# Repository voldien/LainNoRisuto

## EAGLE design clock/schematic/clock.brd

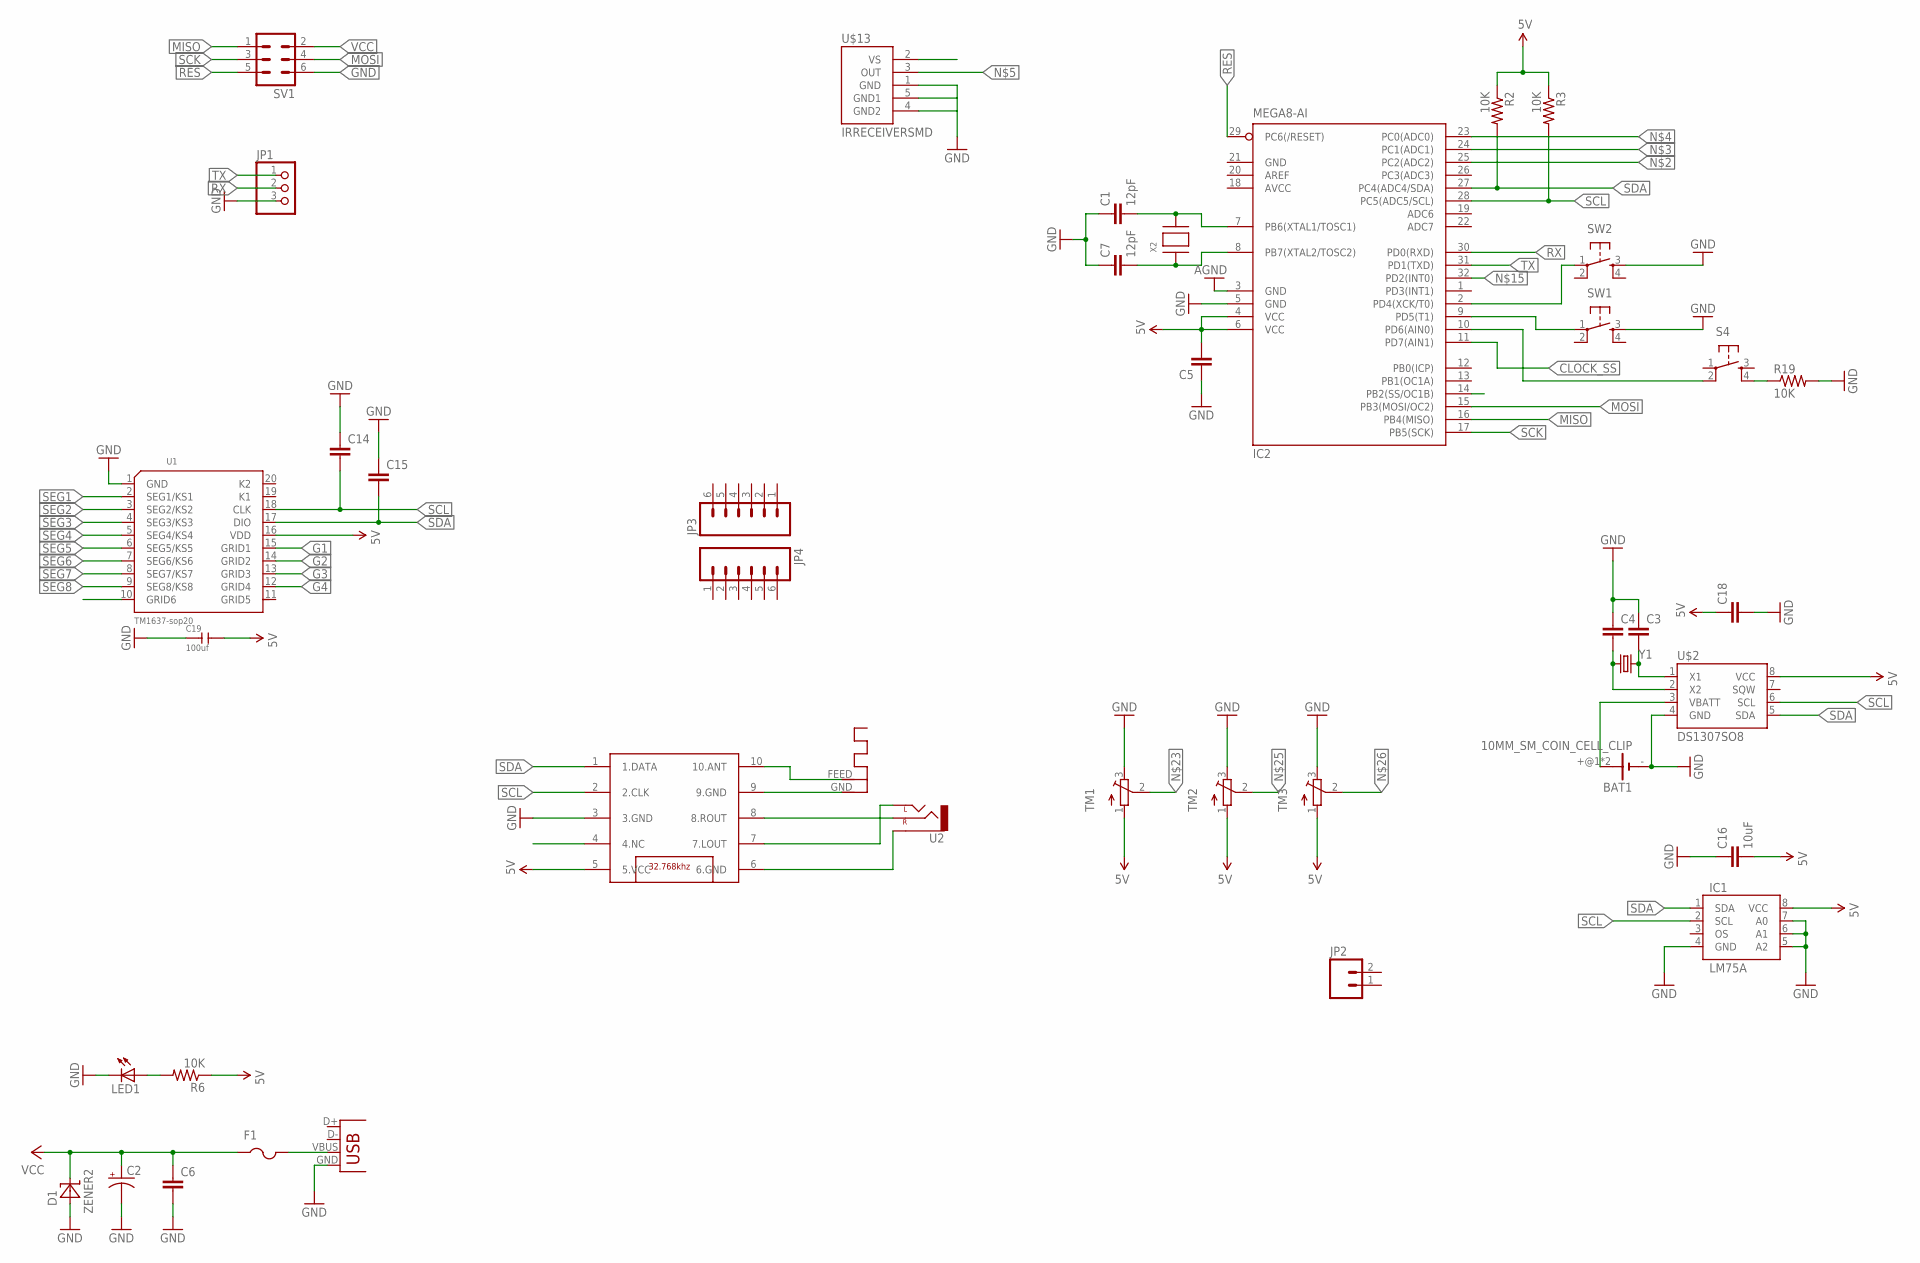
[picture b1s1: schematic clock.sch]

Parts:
ANT1: ANTENNA; RN-ANT
BAT1: 10MM_SM_COIN_CELL_CLIP
C1, C7: 12pF; C0603
C2: CPOL-USB; PANASONIC_B
C3, C4, C5, C6, C14, C15, C18: C-EUC0603; C0603
C16: 10uF; C0603
C19: 100uf; C1206
D1: ZENER2; SOD123
F1: PTCFUSE-1206; R1206
IC1: LM75A; SO8
IC2: MEGA8-AI; TQFP32-08
JP1: PINHD-1X3CB; 1X03-CLEANBIG
JP2: M02PTH; 1X02
JP3, JP4: M06SIP; 1X06
LED1: LED0603; LED-0603
R2, R3, R6, R19: 10K; R0603
S4: TAC_SWITCHSMD; TACTILE_SWITCH_SMD
SV1: MA03-2
SW1, SW2: TAC_SWITCHSMD; TACTILE_SWITCH_SMD
TM1, TM2, TM3: TRIMPOTTC33X; TC33X
U1: TM1637-sop20; SOP20-1.27-12.7X7.65MM
U2: AUDIO-JACKSMD; STEREOJACK2.5MM_SMD
U$2: DS1307SO8; SO08
U$13: IRRECEIVERSMD; TSOP8523
U$14: TEA5767; TJ-102BC
X1: USB-MICROB
X2: XTAL-3.2X1.5; XTAL3215
Y1: CRYSTALTC26H; TC26H

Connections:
5V: C5.2, C16.2, C18.1, C19.2, IC1.8 (VCC), IC2.4 (VCC), IC2.6 (VCC), R2.1, R3.1, R6.1, TM1.1 (A), TM2.1 (A), TM3.1 (A), U1.16 (VDD), U$2.8 (VCC), U$14.5 (5.VCC)
AGND: IC2.3 (GND)
AVCC: IC2.18 (AVCC)
CLOCK_SS: IC2.11 (PD7(AIN1))
G1: U1.15 (GRID1)
G2: U1.14 (GRID2)
G3: U1.13 (GRID3)
G4: U1.12 (GRID4)
GND: BAT1.-, C1.1, C2.-, C3.1, C4.1, C5.1, C6.2, C7.1, C14.1, C15.1, C16.1, C18.2, C19.1, D1.A, IC1.4 (GND), IC1.5 (A2), IC1.6 (A1), IC1.7 (A0), IC2.5 (GND), IC2.21 (GND), JP1.3, LED1.C, R19.2, SV1.6, SW1.3, SW2.3, TM1.3 (E), TM2.3 (E), TM3.3 (E), U1.1 (GND), U$2.4 (GND), U$13.1 (GND), U$13.4 (GND2), U$13.5 (GND1), U$14.3 (3.GND), X1.GND
MISO: IC2.16 (PB4(MISO)), SV1.1
MOSI: IC2.15 (PB3(MOSI/OC2)), SV1.4
unnamed: U2.5 (SLEEVE), U$14.6 (6.GND)
unnamed: U2.4 (RIGHT), U$14.8 (8.ROUT)
unnamed: BAT1.+@1 (+), BAT1.+@2 (+), U$2.3 (VBATT)
unnamed: U2.1 (LEFT), U$14.7 (7.LOUT)
unnamed: C4.2, U$2.2 (X2), Y1.1
unnamed: C3.2, U$2.1 (X1), Y1.2
unnamed: ANT1.FEED, U$14.10 (10.ANT)
unnamed: IC2.9 (PD5(T1)), SW1.1
unnamed: ANT1.GND, U$14.9 (9.GND)
unnamed: IC2.2 (PD4(XCK/T0)), SW2.1
unnamed: IC2.10 (PD6(AIN0)), S4.2
unnamed: F1.2, X1.VBUS
unnamed: C1.2, IC2.7 (PB6(XTAL1/TOSC1)), X2.P$2
unnamed: R19.1, S4.4
unnamed: C7.2, IC2.8 (PB7(XTAL2/TOSC2)), X2.P$1
unnamed: LED1.A, R6.2
RES: IC2.29 (PC6(/RESET)), SV1.5
RX: IC2.30 (PD0(RXD)), JP1.2
SCK: IC2.17 (PB5(SCK)), SV1.3
SCL: C14.2, IC1.2 (SCL), IC2.28 (PC5(ADC5/SCL)), R3.2, U1.18 (CLK), U$2.6 (SCL), U$14.2 (2.CLK)
SDA: C15.2, IC1.1 (SDA), IC2.27 (PC4(ADC4/SDA)), R2.2, U1.17 (DIO), U$2.5 (SDA), U$14.1 (1.DATA)
SEG1: U1.2 (SEG1/KS1)
SEG2: U1.3 (SEG2/KS2)
SEG3: U1.4 (SEG3/KS3)
SEG4: U1.5 (SEG4/KS4)
SEG5: U1.6 (SEG5/KS5)
SEG6: U1.7 (SEG6/KS6)
SEG7: U1.8 (SEG7/KS7)
SEG8: U1.9 (SEG8/KS8)
TX: IC2.31 (PD1(TXD)), JP1.1
VCC: C2.+, C6.1, D1.C, F1.1, SV1.2

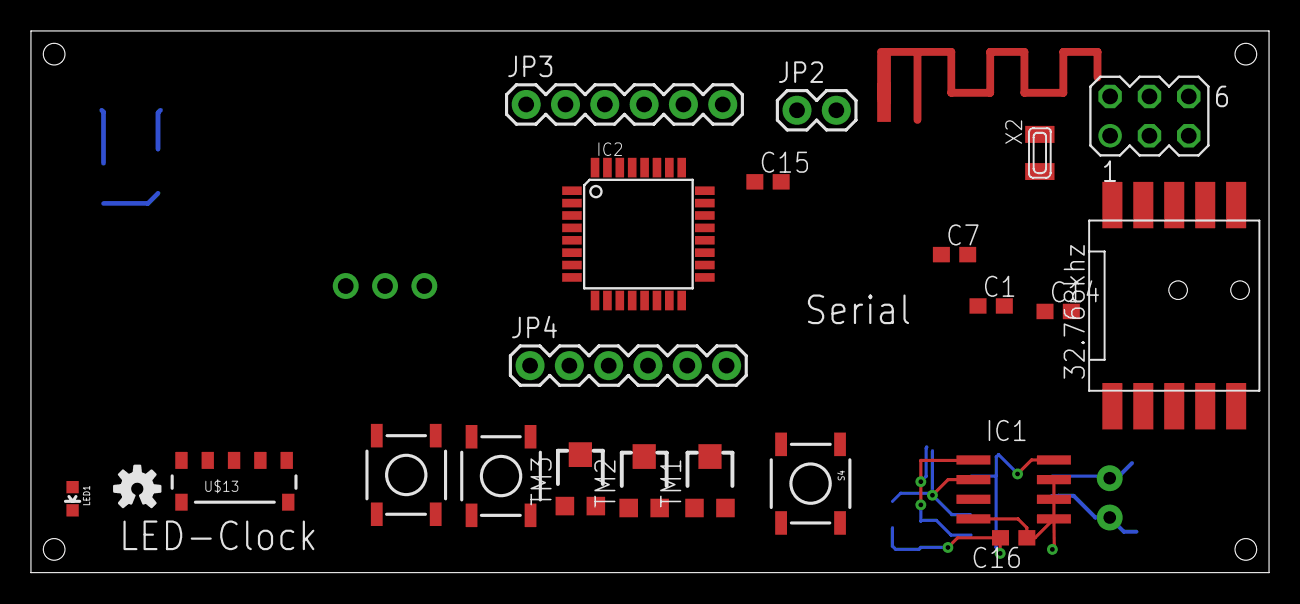
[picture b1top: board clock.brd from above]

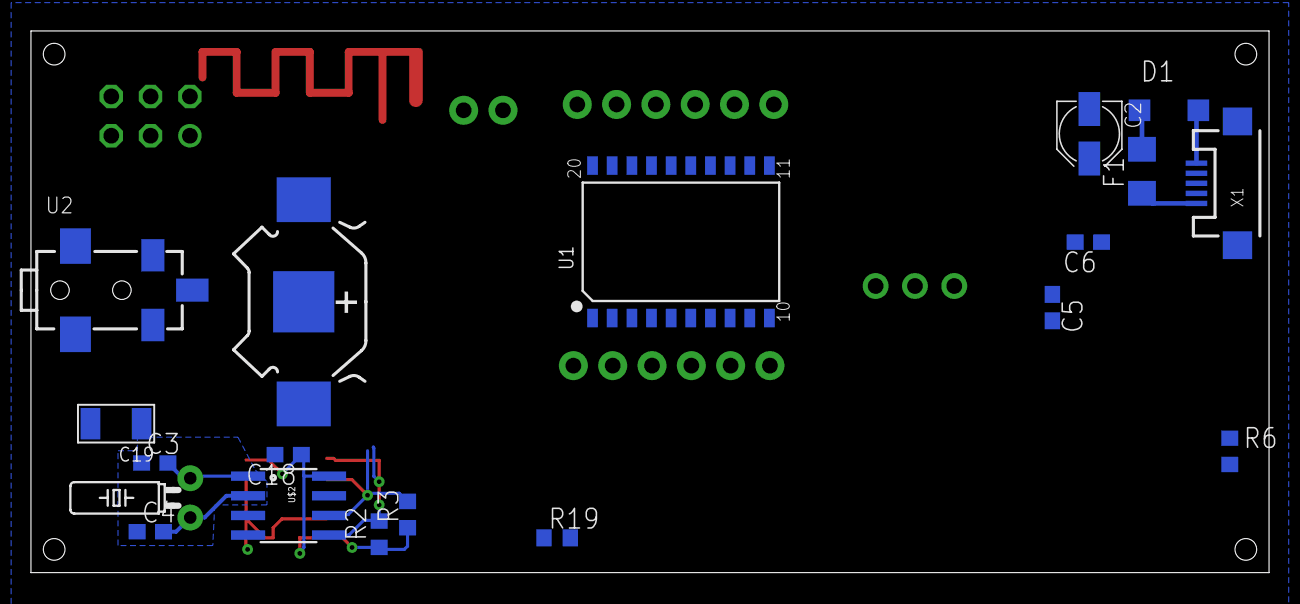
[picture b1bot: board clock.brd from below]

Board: 2 copper layers, 80.0 x 35.0 mm, 43 parts (19 on the bottom side), 27 nets.

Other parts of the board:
U$6: OSHW-LOGO-S

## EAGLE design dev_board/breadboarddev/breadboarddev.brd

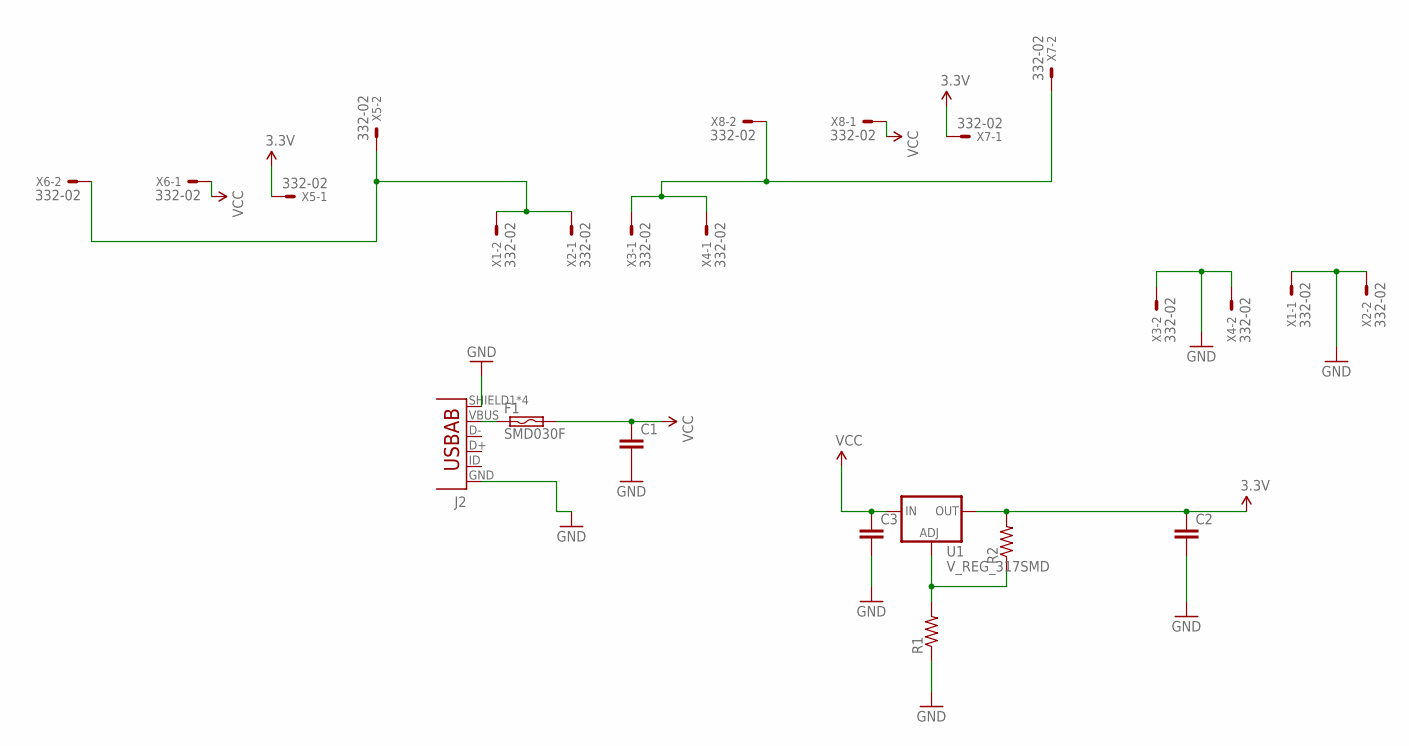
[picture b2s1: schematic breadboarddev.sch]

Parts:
C1, C2, C3: C-EUC0603K; C0603K
F1: SMD030F; SMD050F
J2: USB-AB; USB-AB-MICRO-SMD
R1, R2: R-US_MELF0204W; MINI_MELF-0204W
U1: V_REG_317SMD; SOT223
X1, X2, X3, X4, X5, X6, X7, X8: 332-02

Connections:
3.3V: C2.1, R2.2, U1.2 (OUT), X5.1, X7.1
GND: C1.2, C2.2, C3.2, J2.GND, J2.SHIELD1 (SHIELD), J2.SHIELD2 (SHIELD), J2.SHIELD3 (SHIELD), J2.SHIELD4 (SHIELD), R1.1, X1.1, X2.2, X3.2, X4.2
unnamed: R1.2, R2.1, U1.1 (ADJ)
unnamed: X1.2, X2.1, X5.2, X6.2
unnamed: F1.1, J2.VBUS
unnamed: X3.1, X4.1, X7.2, X8.2
VCC: C1.1, C3.1, F1.2, U1.3 (IN), X6.1, X8.1

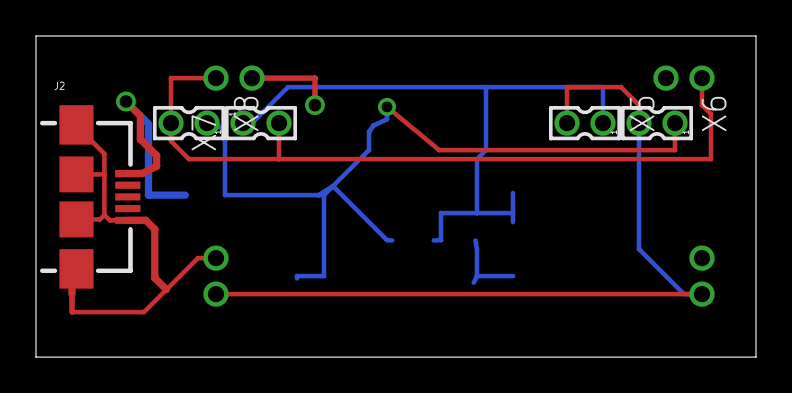
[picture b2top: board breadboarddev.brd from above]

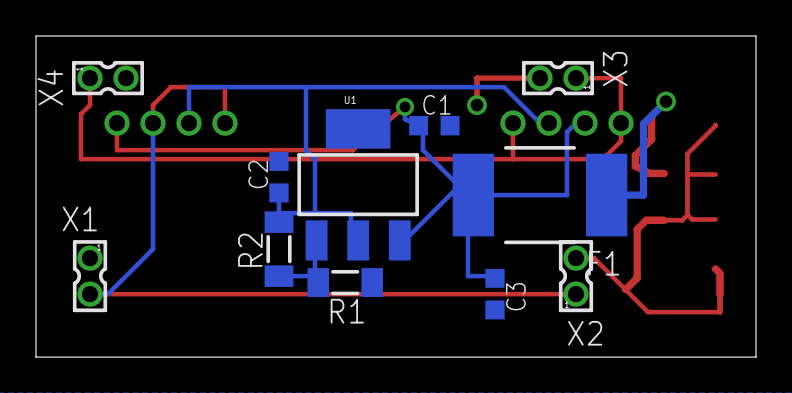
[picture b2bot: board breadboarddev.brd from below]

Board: 2 copper layers, 40.0 x 17.8 mm, 17 parts (11 on the bottom side), 7 nets.

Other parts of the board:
U$1: OSHWLOGO_TOL_0.2

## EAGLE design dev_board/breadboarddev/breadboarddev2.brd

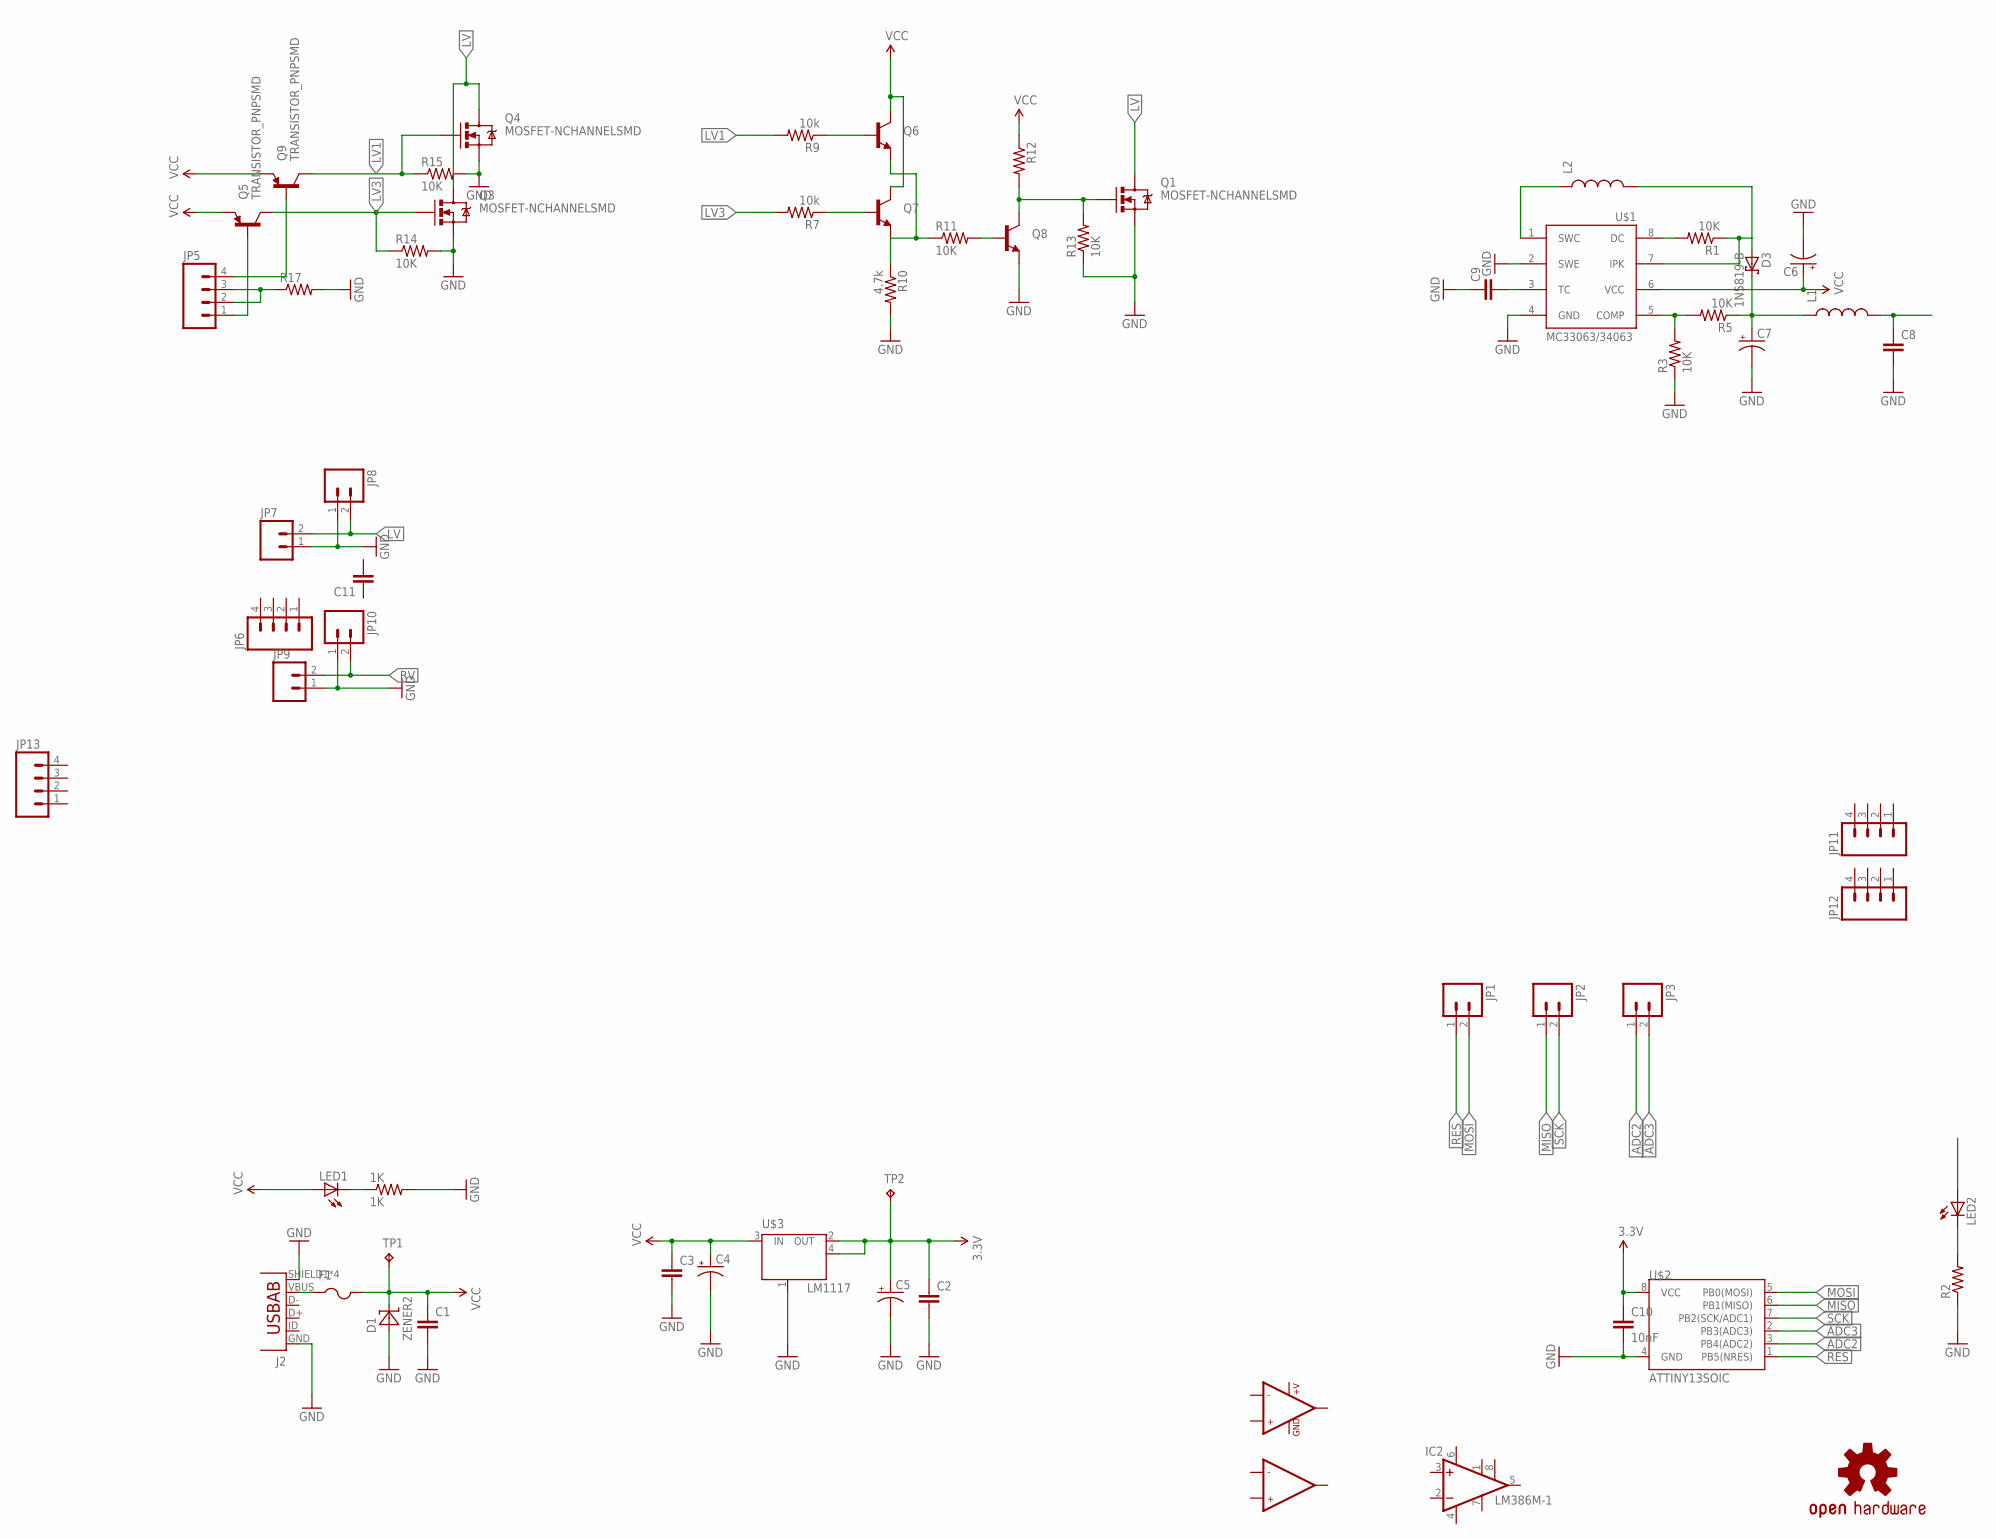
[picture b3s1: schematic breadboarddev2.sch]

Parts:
1K: 1K; R0603
C1, C2, C3, C9, C11: C-EUC0603K; C0603K
C4, C5, C6, C7: CPOL-US153CLV-0405; 153CLV-0405
C8: CAP1206; 1206
C10: 10nF; C0603K
D1: ZENER2; SOD123
D3: 1N5819-B; DO41-7.6
F1: PTCFUSE-1206; R1206
IC2: LM386M-1; SO08
J2: USB-AB; USB-AB-MICRO-SMD
JP1, JP2, JP3, JP7, JP8, JP9, JP10: M021X02_NO_SILK; 1X02_NO_SILK
JP5, JP6, JP11, JP12, JP13: M04PTH; 1X04
L1: INDUCTOR0603; 0603
L2: INDUCTOR.; CDRH2D09
LED1: LEDCHIP-LED0603; CHIP-LED0603
LED2: LED0603; LED-0603
Q1, Q3, Q4: MOSFET-NCHANNELSMD; SOT23-3
Q5, Q9: TRANSISTOR_PNPSMD; SOT23-3
Q6, Q7, Q8: TRANSISTOR_NPNSOT23; SOT23
R1, R3, R5, R11, R13, R14, R15: 10K; R0603
R2, R12, R17: R-US_R0603; R0603
R7, R9: 10k; R0603
R10: 4.7k; R0603
TP1, TP2: TPB1,27; B1,27
U$1: MC33063/MC34063D; SO08
U$2: ATTINY13SOIC; SO08
U$3: LM1117; SOT223
U$4: LMV358; SO08
U$5: OSHW-LOGOS; OSHW-LOGO-S

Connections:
3.3V: C2.1, C5.+, C10.1, TP2.TP, U$2.8 (VCC), U$3.2 (OUT), U$3.4 (OUT)
+V: U$4.8 (+V)
ADC2: JP3.1, U$2.3 (PB4(ADC2))
ADC3: JP3.2, U$2.2 (PB3(ADC3))
GND: 1K.2, C1.2, C2.2, C3.2, C4.-, C5.-, C6.-, C7.-, C8.2, C9.1, C10.2, D1.A, IC2.4 (GND), J2.GND, J2.SHIELD1 (SHIELD), J2.SHIELD2 (SHIELD), J2.SHIELD3 (SHIELD), J2.SHIELD4 (SHIELD), JP7.1, JP8.1, JP9.1, JP10.1, Q1.2 (S), Q3.2 (S), Q4.2 (S), Q8.2 (E), R2.1, R3.1, R10.2, R13.1, R14.2, R15.2, R17.2, U$1.2 (SWE), U$1.4 (GND), U$2.4 (GND), U$3.1 (GND/ADJ), U$4.4 (GND)
LV: JP7.2, JP8.2, Q1.3 (D), Q3.3 (D), Q4.3 (D)
LV1: Q4.1 (G), Q9.3 (C), R9.2, R15.1
LV3: Q3.1 (G), Q5.3 (C), R7.2, R14.1
MISO: JP2.1, U$2.6 (PB1(MISO))
MOSI: JP1.2, U$2.5 (PB0(MOSI))
unnamed: LED2.C, R2.2
unnamed: JP5.1, Q5.1 (B)
unnamed: F1.1, J2.VBUS
unnamed: C8.1, L1.2
unnamed: C7.+, D3.C, L1.1, R5.1
unnamed: R3.2, R5.2, U$1.5 (COMP)
unnamed: L2.P$1 (1), U$1.1 (SWC)
unnamed: JP5.4, Q9.1 (B)
unnamed: Q6.1 (B), R9.1
unnamed: Q7.1 (B), R7.1
unnamed: R1.2, U$1.8 (DC)
unnamed: 1K.1, LED1.C
unnamed: Q6.2 (E), Q7.2 (E), R10.1, R11.1
unnamed: D3.A, L2.P$2 (2), R1.1, U$1.7 (IPK)
unnamed: Q8.1 (B), R11.2
unnamed: Q1.1 (G), Q8.3 (C), R12.2, R13.2
unnamed: C9.2, U$1.3 (TC)
unnamed: JP5.2, JP5.3, R17.1
RES: JP1.1, U$2.1 (PB5(NRES))
RV: JP9.2, JP10.2
SCK: JP2.2, U$2.7 (PB2(SCK/ADC1))
VCC: C1.1, C3.1, C4.+, C6.+, D1.C, F1.2, LED1.A, Q5.2 (E), Q6.3 (C), Q7.3 (C), Q9.2 (E), R12.1, TP1.TP, U$1.6 (VCC), U$3.3 (IN)
VS: IC2.6 (VS)

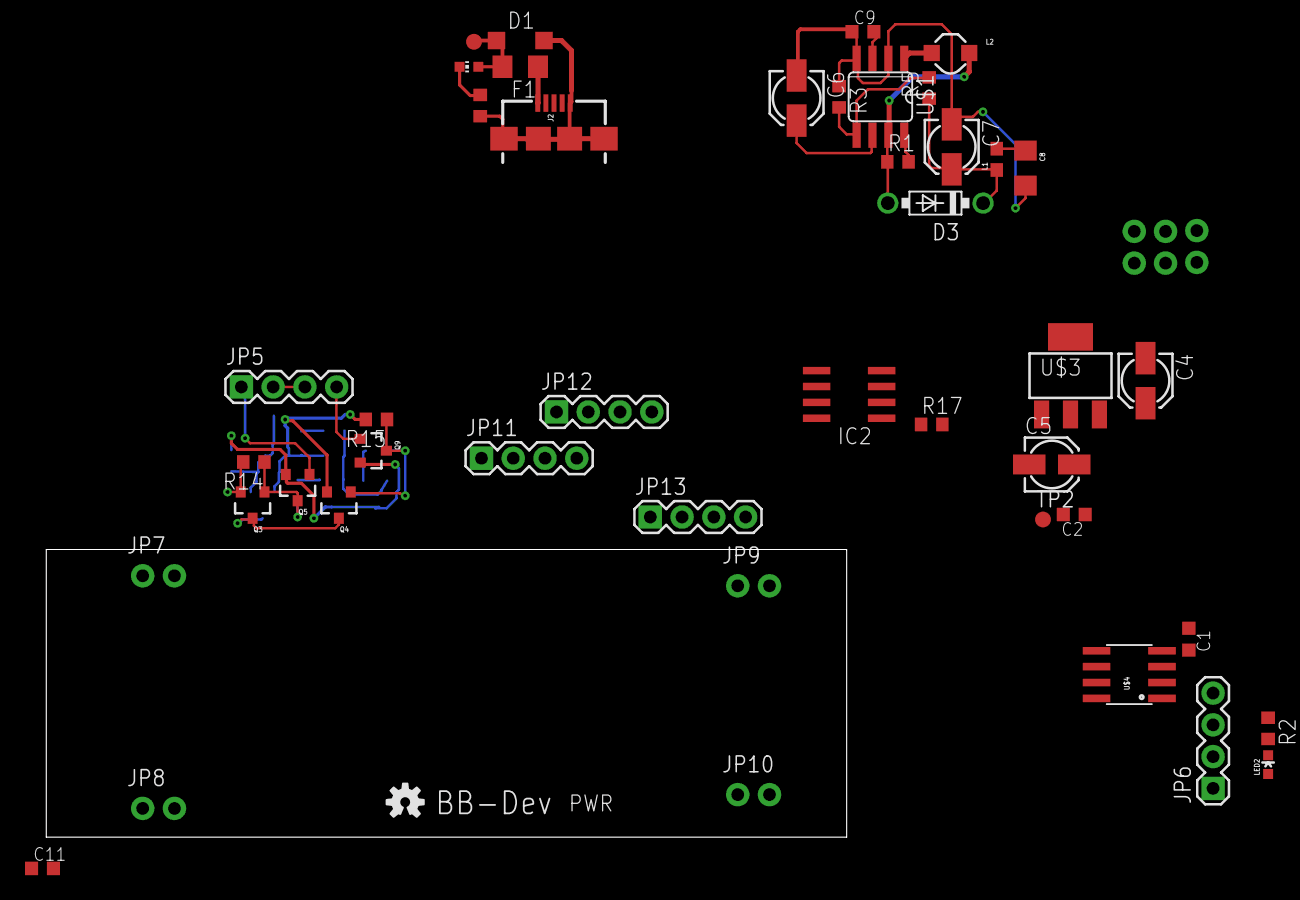
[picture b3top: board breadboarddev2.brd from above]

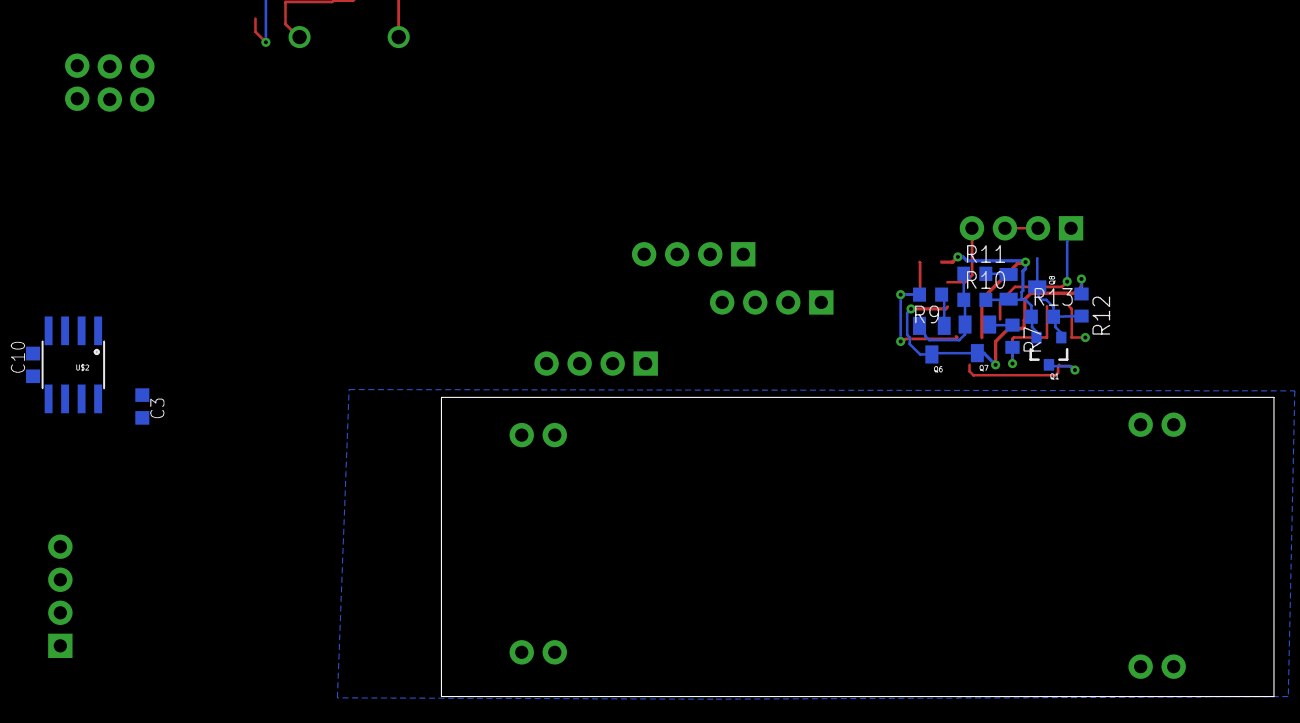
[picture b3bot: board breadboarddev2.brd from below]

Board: 2 copper layers, 61 parts (13 on the bottom side), 31 nets.

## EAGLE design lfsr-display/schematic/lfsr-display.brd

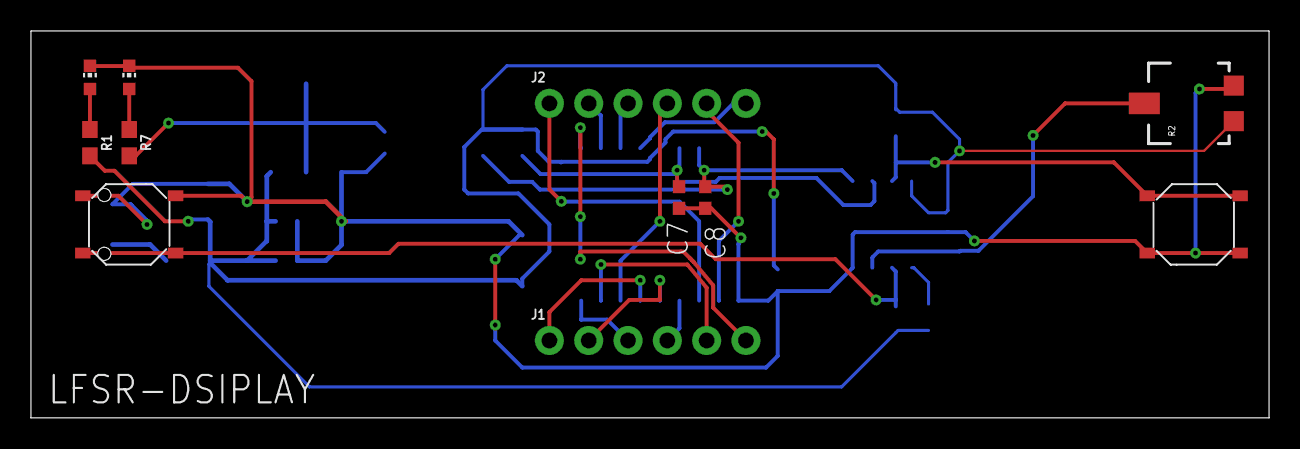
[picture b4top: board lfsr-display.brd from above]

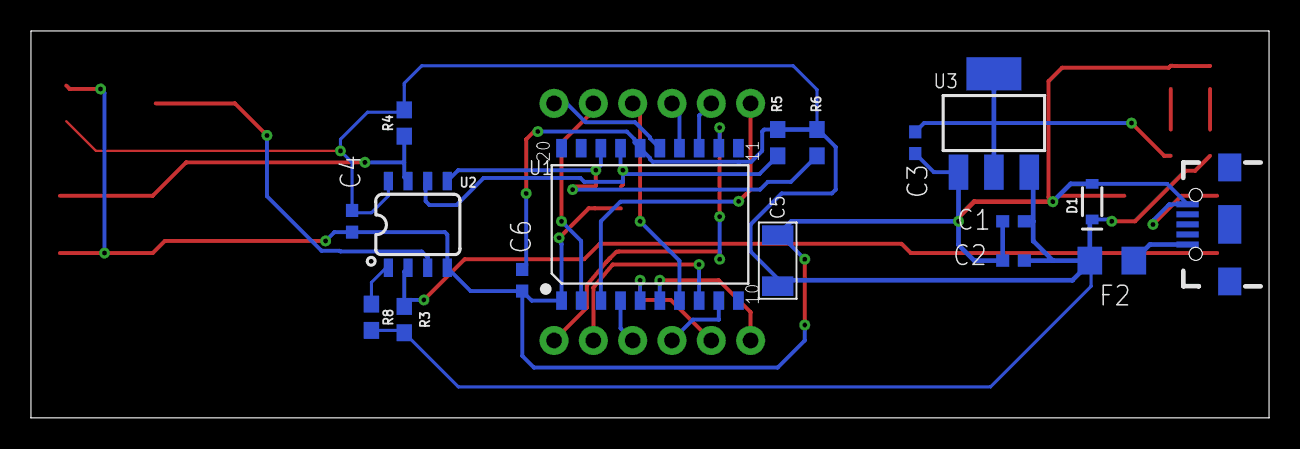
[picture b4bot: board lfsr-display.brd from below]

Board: 2 copper layers, 80.0 x 25.0 mm, 28 parts (17 on the bottom side), 24 nets.

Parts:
C1: 10uF; RESC0603_L
C2, C4: 100nF; RESC0603_L
C3: 100uF; RESC0603_L
C5: 100uf; C1206
C6: 100NF; RESC0603_L
C7, C8: 100pF; RESC0603_L
D1: 3.6V; SOD-323
F2: R1206
J1, J2: 1X06_NO_SILK
J3: USB-B-MICRO-SMD_RED_PASTE
LED1, LED2: CHIP-LED0603
R1: 480; 0603
R2: TRIMPOT-5MM-V2
R3, R4, R5, R6, R8: 10K; 0603
R7: 220; 0603
SW1, SW2: SKQGADE010; SW4-SMD-5.2X5.2X1.5MM
U1: TM1637-sop20; SOP20-1.27-12.7X7.65MM
U2: ATTINY13SOIC; SO08_MCU
U3: CJT1117-3.3-SOT223; SOT-223

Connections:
3.3V: C3.2, R7.2, U3.2, U3.TER
+5V: C1.2, C2.2, C4.2, C5.2, C6.1, D1.C, F2.1, R1.2, R2.C, R3.2, R4.2, R5.2, R6.2, R8.2, U1.16, U2.8, U3.3
A: J2.5, U1.2
B: J2.1, U1.3
C: J1.4, U1.4
CLK: C8.1, R6.1, U1.18, U2.5
D: J1.2, U1.5
DIO: C7.1, R5.1, U1.17, U2.6
DP: J1.3, U1.9
E: J1.1, U1.6
F: J2.4, U1.7
G: J1.5, U1.8
G1: J2.6, U1.15
G2: J2.3, U1.14
G3: J2.2, U1.13
G4: J1.6, U1.12
GND: C1.1, C2.1, C3.1, C4.1, C5.1, C6.2, C7.2, C8.2, D1.A, J3.GND, LED1.C, LED2.C, R2.A, SW1.3, SW1.4, SW2.3, SW2.4, U1.1, U2.4, U3.1
unnamed: LED1.A, R1.1
unnamed: LED2.A, R7.1
unnamed: F2.2, J3.VBUS
unnamed: R8.1, U2.1
NEXT: R3.1, SW1.1, SW1.2, U2.2
SEED: R4.1, SW2.1, SW2.2, U2.7
SEEDINPUT: R2.B, U2.3

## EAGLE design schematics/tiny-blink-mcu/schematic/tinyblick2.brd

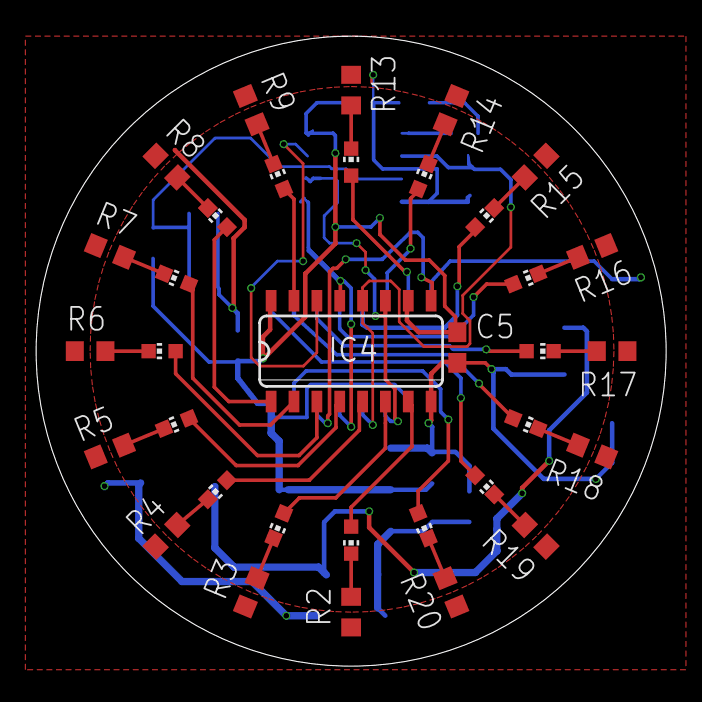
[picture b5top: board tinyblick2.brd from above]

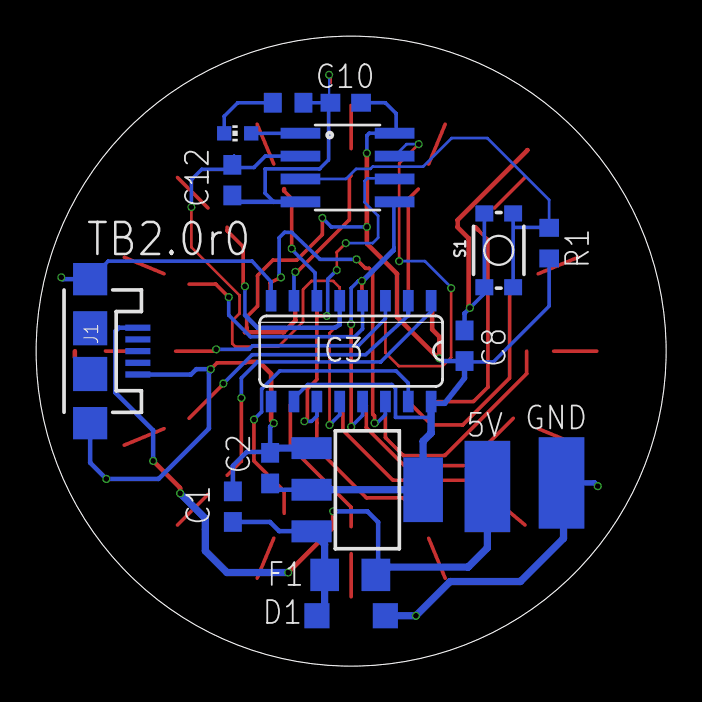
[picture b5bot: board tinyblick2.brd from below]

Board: 2 copper layers, 35.0 x 35.0 mm, 51 parts (17 on the bottom side), 44 nets.

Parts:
5V: WIREPADSMD2,54-5,08; SMD2,54-5,08
C1, C2, C5, C8, C10: 100nF; C0603
C12: 10nF; C0603
D1: ZENER2; SOD123
F1: R1206
GND: WIREPADSMD2,54-5,08; SMD2,54-5,08
IC3, IC4: 74LS595D; SO16
J1: USB-MICROB
LED1, LED2, LED3, LED4, LED5, LED6, LED7, LED8, LED9, LED10, LED11, LED12, LED13, LED14, LED15, LED16, LED17: CHIP-LED0603
R1, R2, R3, R4, R5, R6, R7, R8, R9, R10, R13, R14, R15, R16, R17, R18, R19, R20: R0603
S1: MOMENTARY-SWITCH-SPST-SMD-4.6X2.8MM; TACTILE_SWITCH_SMD_4.6X2.8MM
U$1: LM1117; SOT223
U$2: ATTINY13SOIC; SO08

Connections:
+3V3: C2.1, C5.1, C8.1, C10.1, IC3.10, IC3.16, IC4.10, IC4.16, R1.2, U$1.2, U$1.4, U$2.8
GND: C1.2, C2.2, C5.2, C8.2, C10.2, C12.1, D1.A, GND.1, IC3.8, IC4.8, J1.GND, J1.MT1, J1.MT2, R2.1, R3.1, R4.1, R5.1, R6.1, R7.1, R8.1, R9.1, R10.1, R13.1, R14.1, R15.1, R16.1, R17.1, R18.1, R19.1, R20.1, S1.1, S1.2, U$1.1, U$2.4
LATCH: C12.2, IC3.12, IC4.12, U$2.2
unnamed: LED1.C, R2.2
unnamed: LED17.C, R10.2
unnamed: LED2.C, R3.2
unnamed: LED3.C, R4.2
unnamed: LED9.C, R13.2
unnamed: LED4.C, R5.2
unnamed: LED5.C, R6.2
unnamed: IC4.3, LED5.A
unnamed: LED6.C, R7.2
unnamed: IC4.2, LED6.A
unnamed: LED7.C, R8.2
unnamed: IC4.1, LED7.A
unnamed: LED8.C, R9.2
unnamed: IC4.15, LED8.A
unnamed: IC4.7, LED1.A
unnamed: C1.1, D1.C, F1.1, U$1.3
unnamed: IC4.6, LED2.A
unnamed: IC4.5, LED3.A
unnamed: LED10.C, R14.2
unnamed: LED11.C, R15.2
unnamed: IC4.4, LED4.A
unnamed: LED12.C, R16.2
unnamed: LED13.C, R17.2
unnamed: IC3.3, LED13.A
unnamed: LED14.C, R18.2
unnamed: IC3.2, LED14.A
unnamed: LED15.C, R19.2
unnamed: IC3.1, LED15.A
unnamed: LED16.C, R20.2
unnamed: IC3.15, LED16.A
unnamed: IC3.7, LED9.A
unnamed: IC3.6, LED10.A
unnamed: IC3.5, LED11.A
unnamed: IC3.4, LED12.A
unnamed: IC3.14, IC4.9
NRES: LED17.A, U$2.1
PB4: R1.1, S1.3, S1.4, U$2.3
PWM: IC3.13, IC4.13, U$2.5
RCLK: IC3.11, IC4.11, U$2.6
SER: IC4.14, U$2.7
VCC: 5V.1, F1.2, J1.VBUS

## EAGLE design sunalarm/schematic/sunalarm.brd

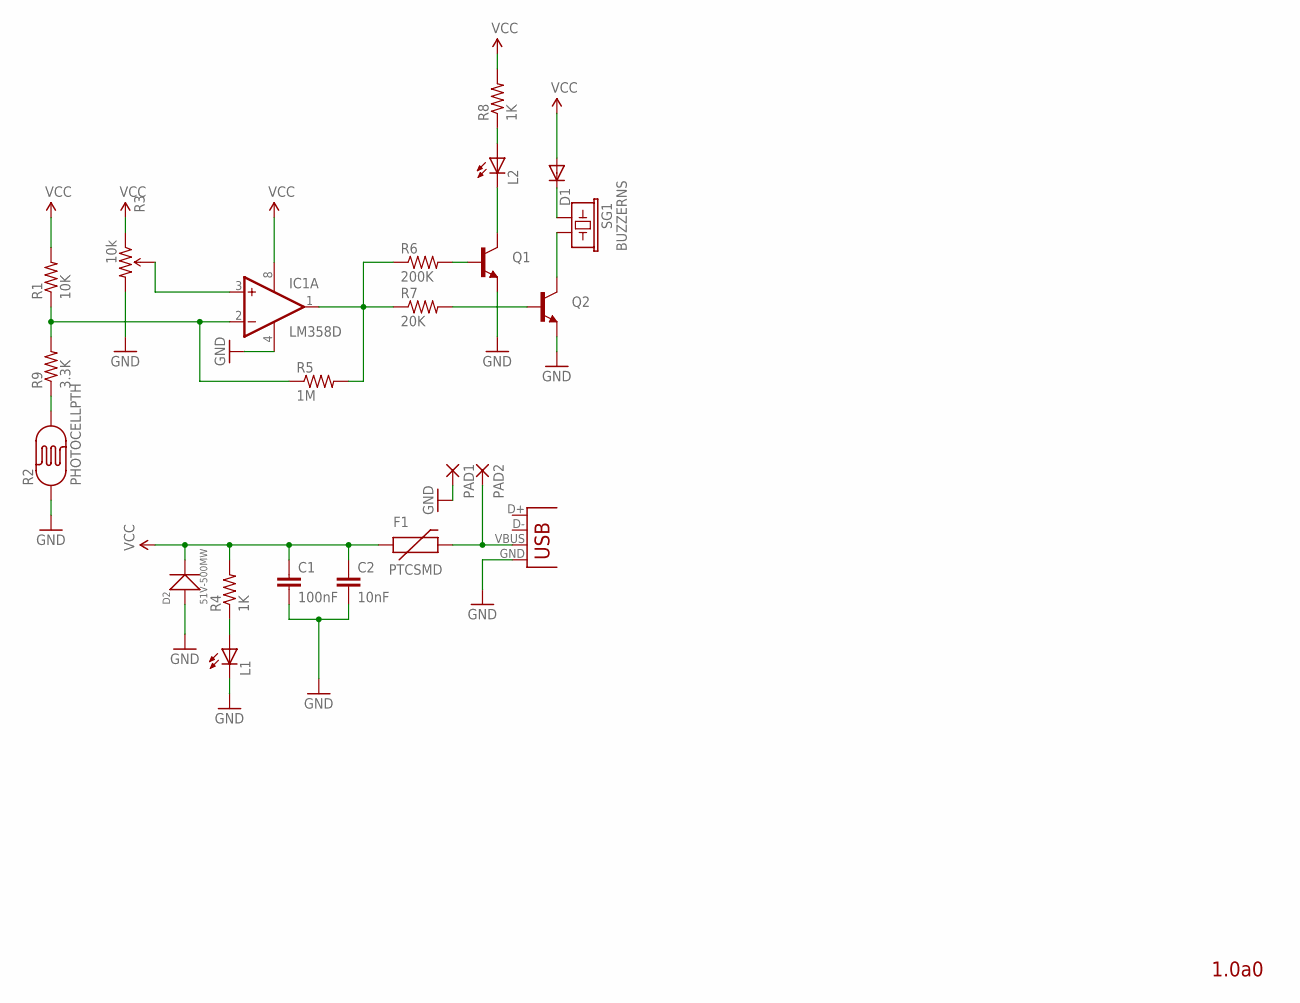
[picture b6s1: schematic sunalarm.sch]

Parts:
C1: 100nF; 0603-CAP
C2: 10nF; 0603-CAP
D1: DIODESOD; SOD-323
D2: 51V-500MW; SOD-123
F1: PTCSMD; PTC-1206
IC1: LM358D; SO08
L1, L2: LED0603; LED-0603
PAD1, PAD2: WIREPADSMD1,27-254; SMD1,27-2,54
Q1, Q2: TRANSISTOR_NPNSOT23; SOT23
R1: 10K; R0603
R2: PHOTOCELLPTH; PHOTOCELL
R3: 10k; TRIMPOT-3MM
R4, R8: 1K; R0603
R5: 1M; R0603
R6: 200K; R0603
R7: 20K; R0603
R9: 3.3K; R0603
SG1: BUZZERNS; BUZZER-12MM-NS
X1: USB-MICROB

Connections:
GND: C1.2, C2.2, D2.+, IC1.4 (V-), L1.C, PAD1.1, Q1.2 (E), Q2.2 (E), R2.1, R3.3 (CW), X1.GND
unnamed: IC1.1 (OUT), R5.2, R6.1, R7.1
unnamed: Q2.1 (B), R7.2
unnamed: F1.2, PAD2.1, X1.VBUS
unnamed: Q2.3 (C), SG1.- (2)
unnamed: L1.A, R4.1
unnamed: R2.2, R9.1
unnamed: IC1.3 (+IN), R3.2 (WIPER)
unnamed: IC1.2 (-IN), R1.1, R5.1, R9.2
unnamed: D1.1 (C), SG1.+ (1)
unnamed: Q1.1 (B), R6.2
unnamed: L2.C, Q1.3 (C)
unnamed: L2.A, R8.1
VCC: C1.1, C2.1, D1.2 (A), D2.-, F1.1, IC1.8 (V+), R1.2, R3.1 (CCW), R4.2, R8.2

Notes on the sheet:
1.0a0

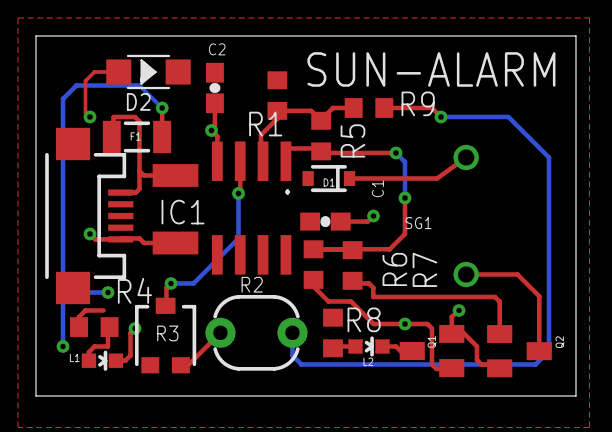
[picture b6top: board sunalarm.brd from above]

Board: 2 copper layers, 30.0 x 20.0 mm, 23 parts (0 on the bottom side), 14 nets.

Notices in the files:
parts and their libraries:
SparkFun: Licensing: CC v3.0 Share-Alike You are welcome to use this library for commercial purposes.
SparkFun-Aesthetics: Licensing: Creative Commons ShareAlike 4.0 International - https://creativecommons.org/licenses/by-sa/4.0
